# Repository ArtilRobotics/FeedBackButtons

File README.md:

# FeedBackButtons
Un dispositivo IoT para tomar feedback fácilmente.

Coloque la pregunta en el panel de la terminal sonriente con papel y el usuario simplemente ingresa la respuesta presionando uno de los cuatro botones en la terminal. Los botones están codificados en cuatro colores, el verde es "muy feliz", el verde amarillo es "feliz", el rosa es "insatisfecho", el rojo es "muy insatisfecho" y las expresiones se dibujan en los botones

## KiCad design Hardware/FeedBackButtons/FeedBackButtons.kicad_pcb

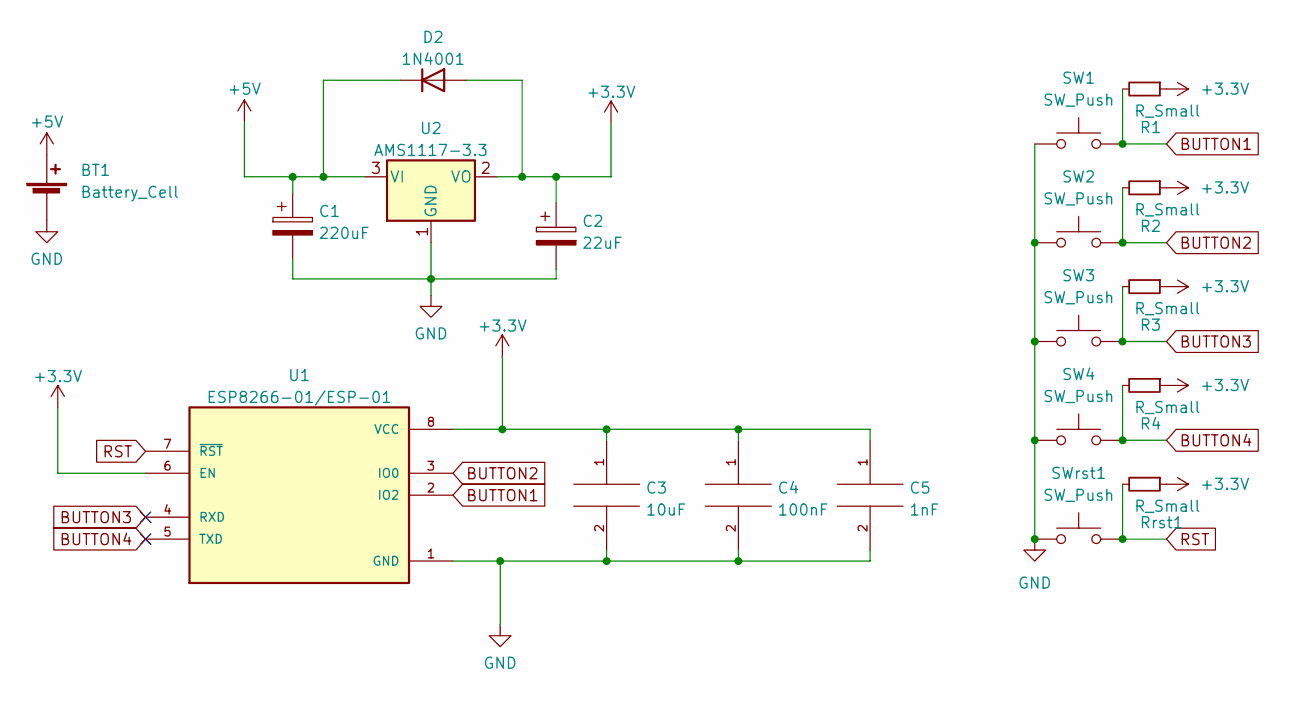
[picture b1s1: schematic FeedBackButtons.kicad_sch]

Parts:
BT1: Battery_Cell; PinHeader_1x02_P2.54mm_Horizontal
C1: 220uF; C_0805_2012Metric_Pad1.18x1.45mm_HandSolder
C2: 22uF; C_0805_2012Metric_Pad1.18x1.45mm_HandSolder
C3: 10uF; C_0805_2012Metric_Pad1.18x1.45mm_HandSolder
C4: 100nF; C_0805_2012Metric_Pad1.18x1.45mm_HandSolder
C5: 1nF; C_0805_2012Metric_Pad1.18x1.45mm_HandSolder
D2: 1N4001; D_DO-41_SOD81_P10.16mm_Horizontal
R1, R2, R3, R4: R_Small; R_0805_2012Metric_Pad1.20x1.40mm_HandSolder
Rrst1: R_Small; R_0805_2012Metric_Pad1.20x1.40mm_HandSolder
SW1, SW2, SW3, SW4: SW_Push; SW_BUTT-2
SWrst1: SW_Push; SW_BUTT-2
U1: ESP8266-01/ESP-01; XCVR_ESP8266-01_ESP-01; PARTREV V1.2
U2: AMS1117-3.3; SOT-223-3_TabPin2

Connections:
+3.3V: C2.1, C3.1, C4.1, C5.1, D2.2 (A), R1.1, R2.1, R3.1, R4.1, Rrst1.1, U1.6 (EN), U1.8 (VCC), U2.2 (VO)
+5V: BT1.1 (+), C1.1, D2.1 (K), U2.3 (VI)
BUTTON1: R1.2, SW1.2, U1.2 (IO2)
BUTTON2: R2.2, SW2.2, U1.3 (IO0)
BUTTON3: R3.2, SW3.2, U1.4 (RXD)
BUTTON4: R4.2, SW4.2, U1.5 (TXD)
GND: BT1.2 (-), C1.2, C2.2, C3.2, C4.2, C5.2, SW1.1, SW2.1, SW3.1, SW4.1, SWrst1.1, U1.1 (GND), U2.1 (GND)
RST: Rrst1.2, SWrst1.2, U1.7 (~RST)

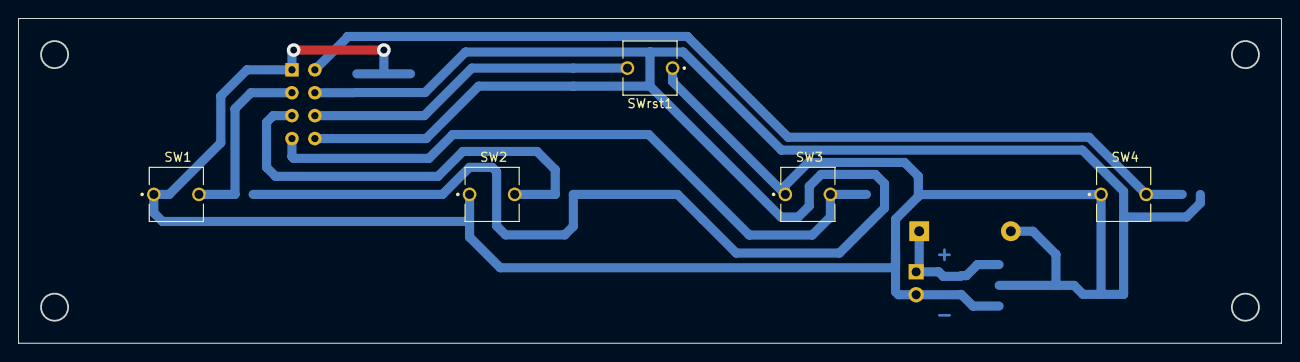
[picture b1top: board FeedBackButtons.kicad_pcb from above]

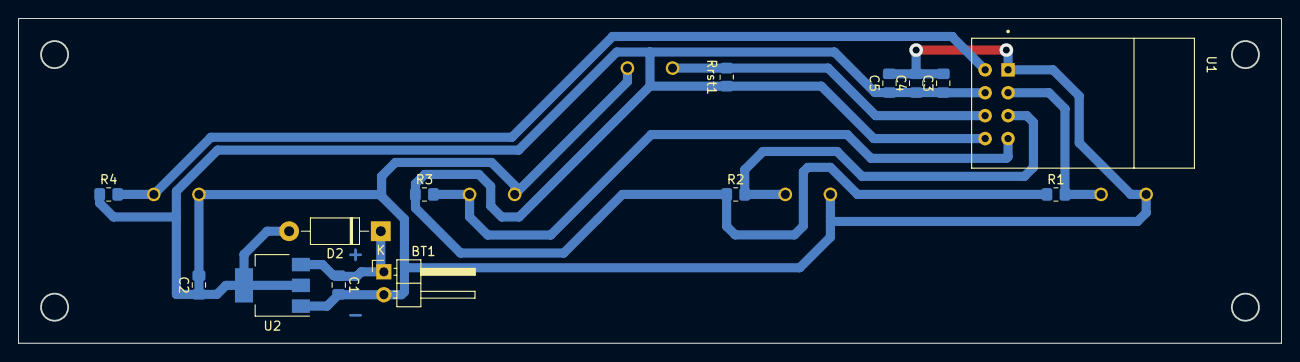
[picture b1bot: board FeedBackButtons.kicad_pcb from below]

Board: 2 copper layers, 139.9 x 35.9 mm, 19 parts (14 on the bottom side), 8 nets.

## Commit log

2022-09-19 Esquema base desde IoTmd
2022-09-19 Diseño esquematico y pcb con ruteado
2022-09-21 Corrección de Agujeros para sujeción
2022-09-21 Genere los Gerbers para fabricacion Demo V1
2022-09-21 ensamble final y DFX
